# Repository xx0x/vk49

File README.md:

# VK49 2.0

Made by Vaclav Mach (vaclavmach at hotmail.cz)

## License 

- Hardware: CC BY-SA 4.0
- Software: CC BY-SA 4.0
- Original sounds: Copyrighted

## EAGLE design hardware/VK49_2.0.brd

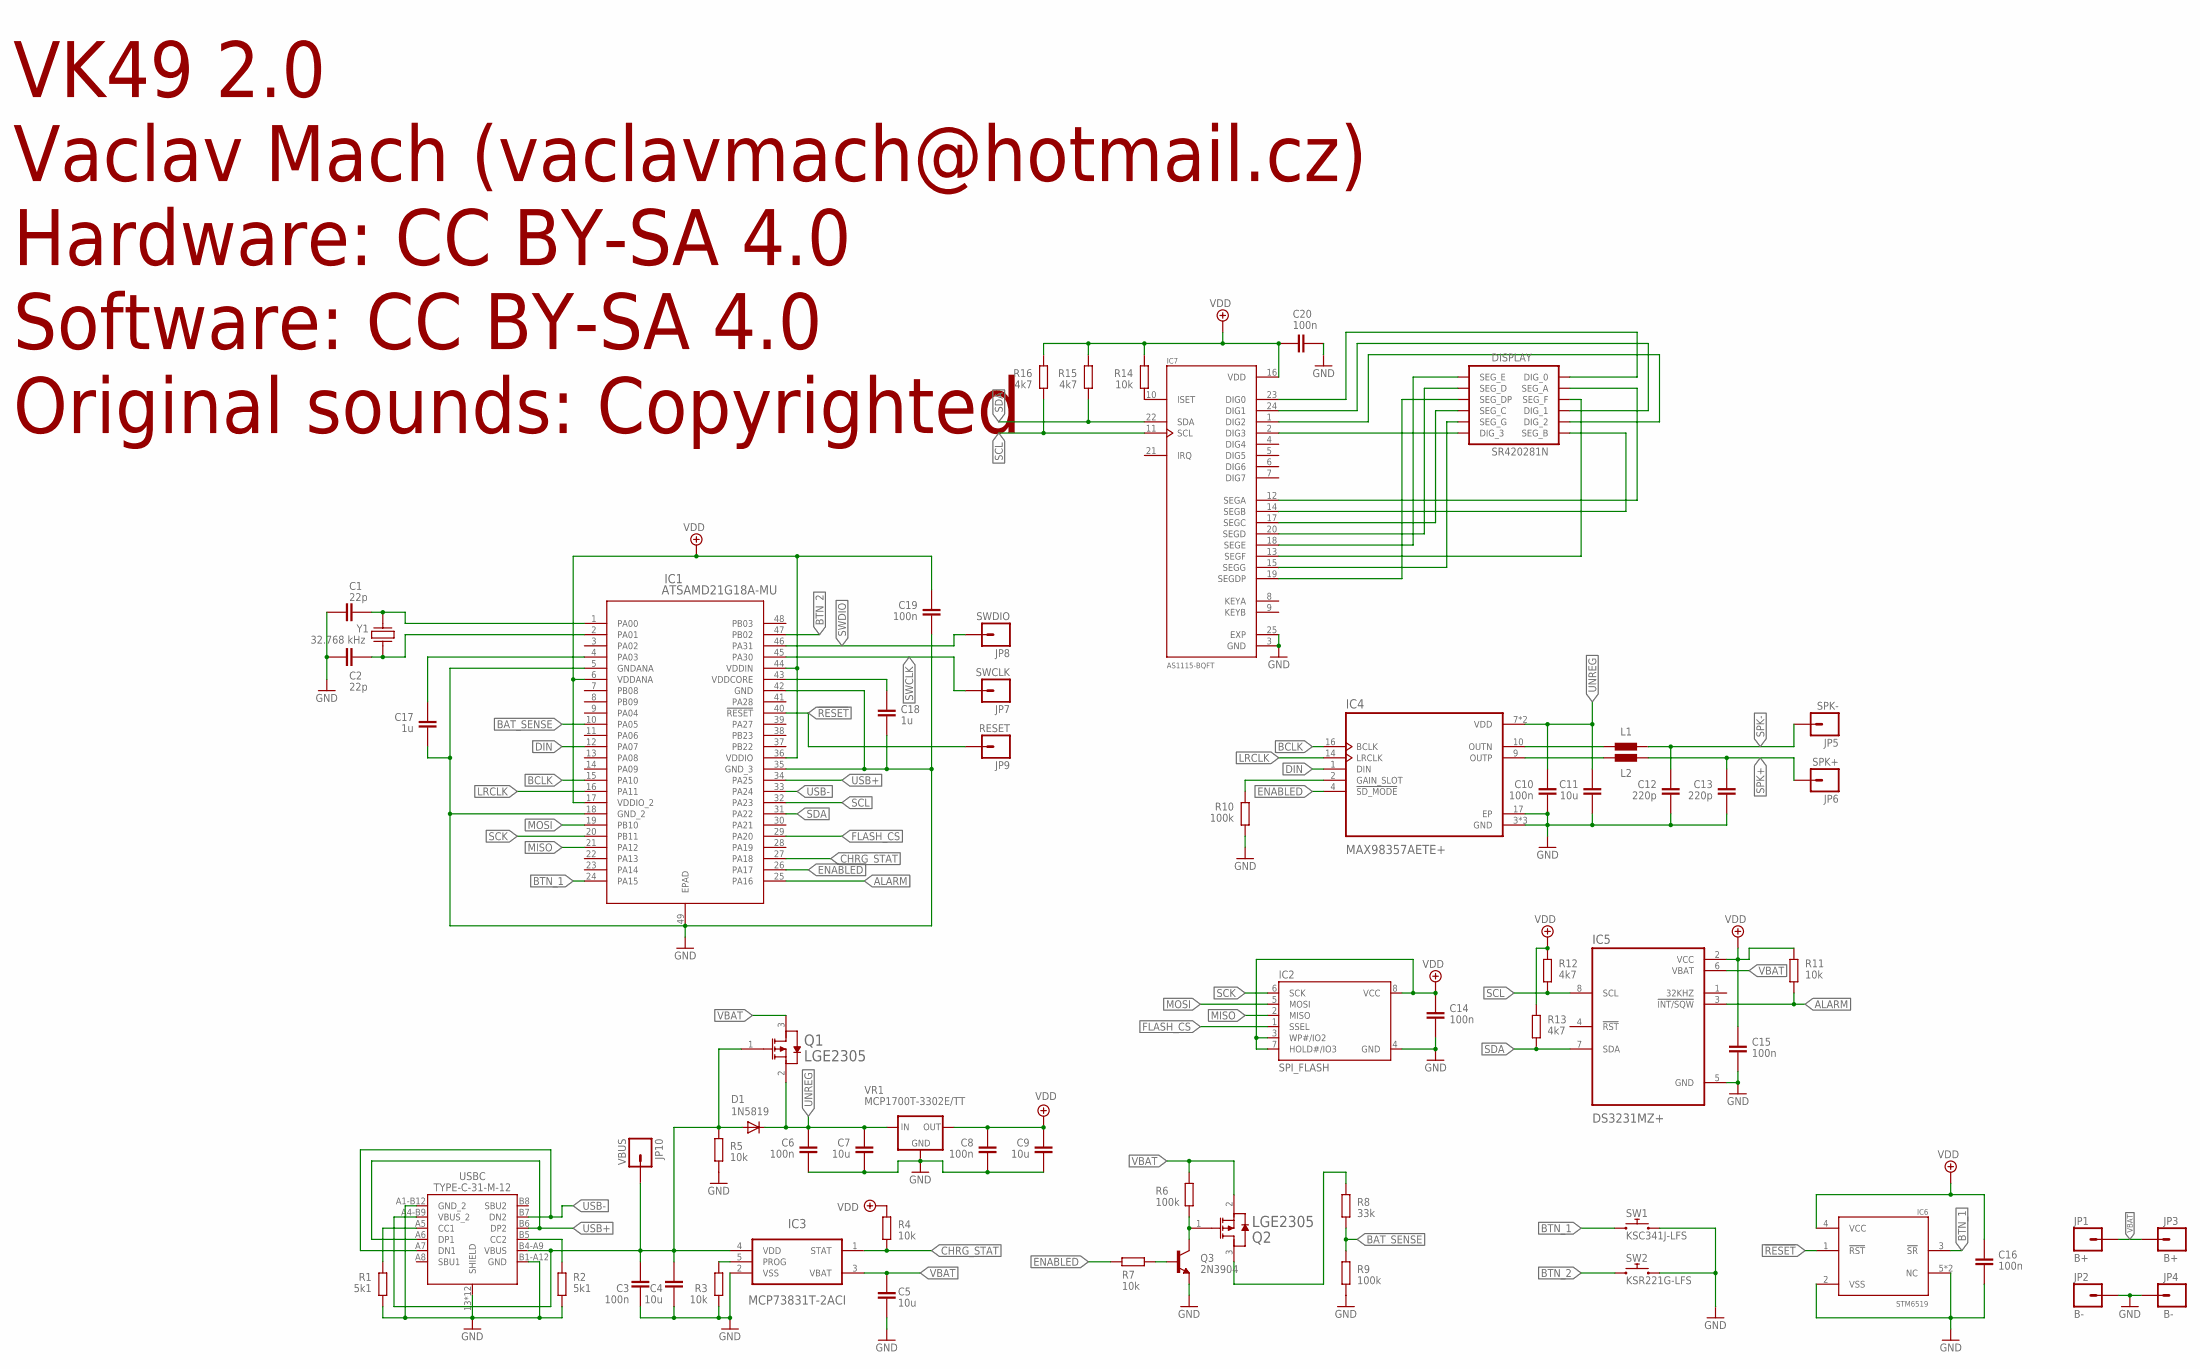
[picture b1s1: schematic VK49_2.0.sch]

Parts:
C1, C2: 22p; CAPACITOR0603
C3, C6, C8, C10, C14, C15, C16, C19, C20: 100n; CAPACITOR0603
C4, C5, C7, C9, C11: 10u; CAPACITOR0805
C12, C13: 220p; CAPACITOR0603
C17, C18: 1u; CAPACITOR0603
D1: 1N5819; SOD123
DISPLAY: SR420281N; SEG_SR420281N_NO-SILK
IC1: ATSAMD21G18A-MU; QFN-48-7X7
IC2: SPI_FLASH; SO08-EIAJ
IC3: MCP73831T-2ACI; SOT23-5
IC4: MAX98357AETE+; QFN50P300X300X80-17N
IC5: DS3231MZ+; SO8
IC6: STM6519; SON50P145X100X65-6N
IC7: AS1115-BQFT; QFN50P400X400X65-25N
JP1, JP3: B+; 1X01_ROUND_NOSILK
JP2, JP4: B-; 1X01_ROUND_NOSILK
JP5: SPK-; 1X01_ROUND_NOSILK
JP6: SPK+; 1X01_ROUND_NOSILK
JP7: SWCLK; 1X01_ROUND_NOSILK
JP8: SWDIO; 1X01_ROUND_NOSILK
JP9: RESET; 1X01_ROUND_NOSILK
JP10: VBUS; 1X01_ROUND_NOSILK
L1, L2: MMZ1608B121CTAH0; 0603
Q1, Q2: LGE2305; SOT23
Q3: 2N3904; SOT23
R1, R2: 5k1; RESISTOR0603
R3, R4, R5, R7, R11, R14: 10k; RESISTOR0603
R6, R9, R10: 100k; RESISTOR0603
R8: 33k; RESISTOR0603
R12, R13, R15, R16: 4k7; RESISTOR0603
SW1: KSC341J-LFS; KSC3XXJ
SW2: KSR221G-LFS; KSR2XXG
USBC: TYPE-C-31-M-12; USB-C
VR1: MCP1700T-3302E/TT; SOT23
Y1: 32.768 kHz; 3.2X1.5-2-PAD

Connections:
!RESET: IC1.40 (!RESET), IC6.1 (!RST), JP9.1
ALARM: IC1.25 (PA16), IC5.3 (!INT/SQW), R11.1
BAT_SENSE: IC1.10 (PA05), R8.2, R9.1
BCLK: IC1.15 (PA10), IC4.16 (BCLK)
BTN_1: IC1.24 (PA15), IC6.3 (!SR), SW1.1, SW1.3 (1)
BTN_2: IC1.47 (PB02), SW2.1
CHRG_STAT: IC1.27 (PA18), IC3.1 (STAT), R4.1
DIN: IC1.12 (PA07), IC4.1 (DIN)
ENABLED: IC1.26 (PA17), IC4.4 (!SD_MODE), R7.1
FLASH_CS: IC1.29 (PA20), IC2.1 (SSEL)
GND: C1.1, C2.1, C3.1, C4.2, C5.2, C6.1, C7.2, C8.1, C9.2, C10.1, C11.2, C12.1, C13.1, C14.1, C15.1, C16.1, C17.1, C18.1, C19.1, C20.1, IC1.5 (GNDANA), IC1.18 (GND_2), IC1.35 (GND_3), IC1.42 (GND), IC1.49 (EPAD), IC2.4 (GND), IC3.2 (VSS), IC4.3 (GND), IC4.11 (GND), IC4.15 (GND), IC4.17 (EP), IC5.5 (GND), IC6.2 (VSS), IC6.5 (NC), IC6.6 (NC), IC7.3 (GND), IC7.25 (EXP), JP2.1, JP4.1, Q3.2 (E), R1.1, R2.1, R3.2, R5.1, R9.2, R10.1, SW1.2, SW1.4 (2), SW2.2, USBC.13 (SHIELD), USBC.14 (SHIELD), USBC.15 (SHIELD), USBC.16 (SHIELD), USBC.A1-B12 (GND_2), USBC.B1-A12 (GND), USBC.S_1_H1 (SHIELD), USBC.S_1_H2 (SHIELD), USBC.S_2_H1 (SHIELD), USBC.S_2_H2 (SHIELD), USBC.S_3_H1 (SHIELD), USBC.S_3_H2 (SHIELD), USBC.S_4_H1 (SHIELD), USBC.S_4_H2 (SHIELD), VR1.GND
LRCLK: IC1.16 (PA11), IC4.14 (LRCLK)
MISO: IC1.21 (PA12), IC2.2 (MISO)
MOSI: IC1.19 (PB10), IC2.5 (MOSI)
unnamed: C1.2, IC1.1 (PA00), Y1.1
unnamed: C2.2, IC1.2 (PA01), Y1.2
unnamed: IC7.10 (ISET), R14.1
unnamed: R1.2, USBC.A5 (CC1)
unnamed: R2.2, USBC.B5 (CC2)
unnamed: C18.2, IC1.43 (VDDCORE)
unnamed: IC3.5 (PROG), R3.1
unnamed: IC4.10 (OUTN), L1.1
unnamed: IC4.9 (OUTP), L2.1
unnamed: IC4.2 (GAIN_SLOT), R10.2
unnamed: C17.2, IC1.4 (PA03)
unnamed: DISPLAY.12 (DIG_0), IC7.23 (DIG0)
unnamed: DISPLAY.9 (DIG_1), IC7.24 (DIG1)
unnamed: DISPLAY.8 (DIG_2), IC7.1 (DIG2)
unnamed: DISPLAY.6 (DIG_3), IC7.2 (DIG3)
unnamed: DISPLAY.11 (SEG_A), IC7.12 (SEGA)
unnamed: DISPLAY.7 (SEG_B), IC7.14 (SEGB)
unnamed: DISPLAY.4 (SEG_C), IC7.17 (SEGC)
unnamed: DISPLAY.2 (SEG_D), IC7.20 (SEGD)
unnamed: DISPLAY.1 (SEG_E), IC7.18 (SEGE)
unnamed: DISPLAY.10 (SEG_F), IC7.13 (SEGF)
unnamed: DISPLAY.5 (SEG_G), IC7.15 (SEGG)
unnamed: DISPLAY.3 (SEG_DP), IC7.19 (SEGDP)
unnamed: Q2.3 (DRAIN), R8.1
unnamed: Q2.1 (GATE), Q3.3 (C), R6.2
unnamed: Q3.1 (B), R7.2
SCK: IC1.20 (PB11), IC2.6 (SCK)
SCL: IC1.32 (PA23), IC5.8 (SCL), IC7.11 (SCL), R12.1, R16.1
SDA: IC1.31 (PA22), IC5.7 (SDA), IC7.22 (SDA), R13.1, R15.1
SPK+: C13.2, JP6.1, L2.2
SPK-: C12.2, JP5.1, L1.2
SWCLK: IC1.45 (PA30), JP7.1
SWDIO: IC1.46 (PA31), JP8.1
UNREG: C6.2, C7.1, C10.2, C11.1, D1.C, IC4.7 (VDD), IC4.8 (VDD), Q1.2 (SOURCE), VR1.VIN (IN)
USB+: IC1.34 (PA25), USBC.A6 (DP1), USBC.B6 (DP2)
USB-: IC1.33 (PA24), USBC.A7 (DN1), USBC.B7 (DN2)
VBAT: C5.1, IC3.3 (VBAT), IC5.6 (VBAT), JP1.1, JP3.1, Q1.3 (DRAIN), Q2.2 (SOURCE), R6.1
VBUS: C3.2, C4.1, D1.A, IC3.4 (VDD), JP10.1, Q1.1 (GATE), R5.2, USBC.A4-B9 (VBUS_2), USBC.B4-A9 (VBUS)
VDD: C8.2, C9.1, C14.2, C15.2, C16.2, C19.2, C20.2, IC1.6 (VDDANA), IC1.17 (VDDIO_2), IC1.36 (VDDIO), IC1.44 (VDDIN), IC2.3 (WP#/IO2), IC2.7 (HOLD#/IO3), IC2.8 (VCC), IC5.2 (VCC), IC6.4 (VCC), IC7.16 (VDD), R4.2, R11.2, R12.2, R13.2, R14.2, R15.2, R16.2, VR1.VOUT (OUT)

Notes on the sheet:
VK49 2.0 Vaclav Mach (vaclavmach@hotmail.cz) Hardware: CC BY-SA 4.0 Software: CC BY-SA 4.0 Original sounds: Copyrighted

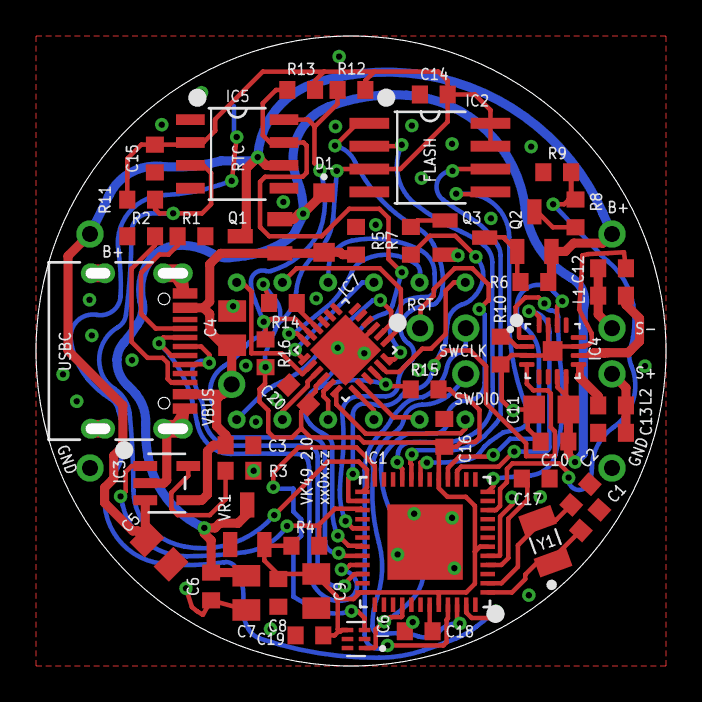
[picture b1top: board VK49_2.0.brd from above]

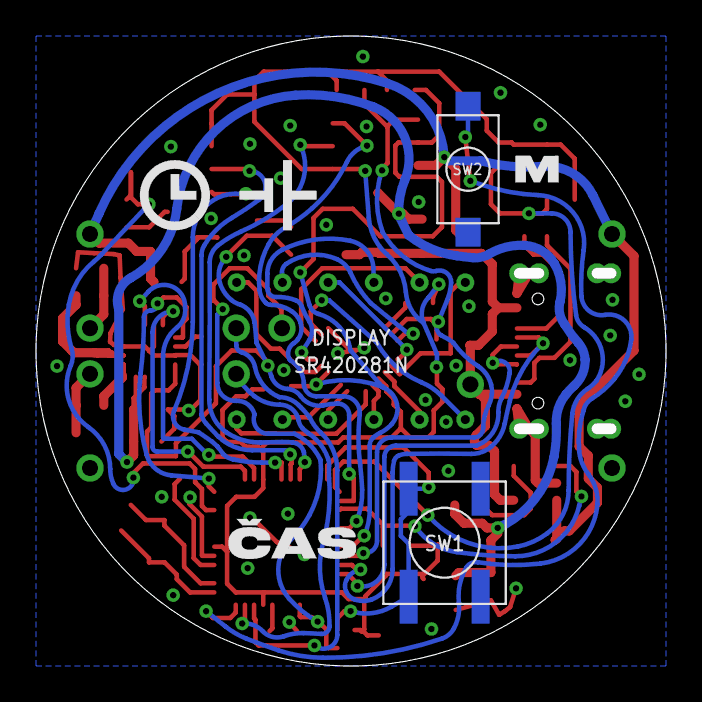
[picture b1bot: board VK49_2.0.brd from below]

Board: 2 copper layers, 34.4 x 34.4 mm, 65 parts (3 on the bottom side), 53 nets.

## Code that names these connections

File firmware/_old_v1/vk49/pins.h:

#define PIN_LED_DATA 10
#define PIN_LED_CLOCK 11
#define PIN_LED_LATCH 12
#define PIN_STATUS_LED 13
#define PIN_FLASH_CS 6
#define PIN_ENABLE 16
#define PIN_BUTTON 5
#define PIN_MENU_BUTTON 19
#define PIN_ALARM 15
#define PIN_BATSENSE 18
#define PIN_I2S_FS 0  // LRC
#define PIN_I2S_SCK 1 // BCLK
#define PIN_I2S_TX 9  // DIN
#define PIN_I2S_RX 2  // BCLK -- not used

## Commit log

2020-07-10 initial code commit
2020-07-11 alarm snooze fix
2020-07-14 correct saySample return value
2020-07-14 disable alarm flashing for better sound quality
2020-07-22 flash memory powerdown / powerup
2020-07-22 display alarm and time in menu, flash sleep fix
2020-08-04 ignore invalid flash data, better startup
2020-08-04 delay updates
2020-08-14 buttons timing update
2020-08-29 add menu timeout, fix timesetting to prevent invalid values
2020-12-05 updates for new samples
2020-12-06 higher debounce time
2020-12-14 update button timeout when sleep
2021-01-05 change code to use AS1115 LED driver
2021-01-05 fix zero indexing
2021-01-14 fix weird display issues by adding delays
2021-01-18 disable message flashing to prevent upload errors
2021-01-18 dont continue saying time when interrupted after setting
2021-01-19 Fix selection of minute and hour samples
2021-05-26 update serial flashing
2021-08-09 fix millis overflow issue
2023-04-30 2.0 hw proposal
2023-04-30 2.0 board in progress
2023-05-01 2.0 board routing
2023-05-01 board update
2023-05-09 finalize, add gerber
2023-06-04 resistor updates
2023-06-04 code update for v2
2023-06-04 better battery reading

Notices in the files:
parts and their libraries:
COPYRIGHT: Copyright (C) 2022 Ultra Librarian. All rights reserved.
